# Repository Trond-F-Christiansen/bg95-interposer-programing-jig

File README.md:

# nRF9151-MK-BG95 interposer programmer

A pogo-pin jig that gives the PCA10196 BG95 interposer (an nRF9151 on a BG95 footprint) power
and a UART AT interface, so the Serial Modem firmware and modem firmware can be programmed and
tested without soldering. SWD is connected with a separate cable.

## Contents

| Folder | What it holds |
|---|---|
| `pcb/` | KiCad project of the pogo-pin plate (`bg95-pogo-plate`), BOM, gerbers in `production/`, and local footprints, 3D models in `lib/` |
| `3d-model/` | 3D-printed frame parts (`.3mf/.step`) and `Assembly.png` |
| `fw/bg95_programmer_at_interface/` | nRF54LM20 DK app: AT shell that forwards typed lines to the interposer |
| `fw/flash_and_verify.py` | Programs modem firmware and app, then checks AT and the modem version |
| `fw/*.hex`, `fw/*.zip` | Serial Modem v2.0.0 release image and modem firmware `mfw_nrf91x1_2.0.4` |

## How it works

Six spring probes land on the BG95 footprint pads of the interposer. The same PCB is used as
upper and lower plate to keep the probes aligned. Receptacles are only soldered into the upper one.

| Header J2 | Signal | BG95 pad | DK pin |
|---|---|---|---|
| 1 | VDD | 32/33 and 52/53 (VBAT_BB, VBAT_RF) | 3.0 V to 5.5 V supply |
| 2 | GND | GND pads | GND |
| 3 | DBG_TX | 23 (interposer TX, P0.15) | P1.04 (UART21 RX) |
| 4 | DBG_RX | 22 (interposer RX, P0.14) | P1.03 (UART21 TX) |

* Supply voltage: **3.0 V to 5.5 V**.
* UART: 115200 8N1, no flow control. The interposer uses 1.8 V I/O, so set the DK's `VDD_IO` to
  **1.8 V**.
* Pads 22 and 23 are adjacent, so their probes are staggered.

## Programming

Hardware: an nRF54LM20 DK running `fw/bg95_programmer_at_interface`, wired to the jig as above.
The DK's on-board debugger is routed out through its debug-out header, with a cable to the
interposer's SWD connector, and programs the nRF9151.

### SWD cable

A custom cable connects the DK's 10-pin debug-out connector to the interposer's 20-pin SWD
connector:

* The 10-pin end plugs into the DK debug-out connector. The 20-pin end plugs into the interposer.
* Pin 1 is pin 1 on both ends, and pins 1 to 10 are wired one-to-one.
* Pins 11 to 20 of the 20-pin connector are left unconnected.

### Flashing

```bash
uv run fw/flash_and_verify.py \
    --port /dev/cu.usbmodem<DK serial>3 \
    --app fw/serial_modem_v2.0.0_interposer_nrf9151_mk_bg95_nrf91m1.hex \
    --modem-fw fw/mfw_nrf91x1_2.0.4.zip
```

The script recovers the device (erases flash and UICR), programs the modem firmware and then the
app, resets, and checks that `AT` returns `OK` and `AT+CGMR` reports the expected modem firmware.
`--sn` is only needed if more than one J-Link is connected. `--port` is the DK's VCOM port.

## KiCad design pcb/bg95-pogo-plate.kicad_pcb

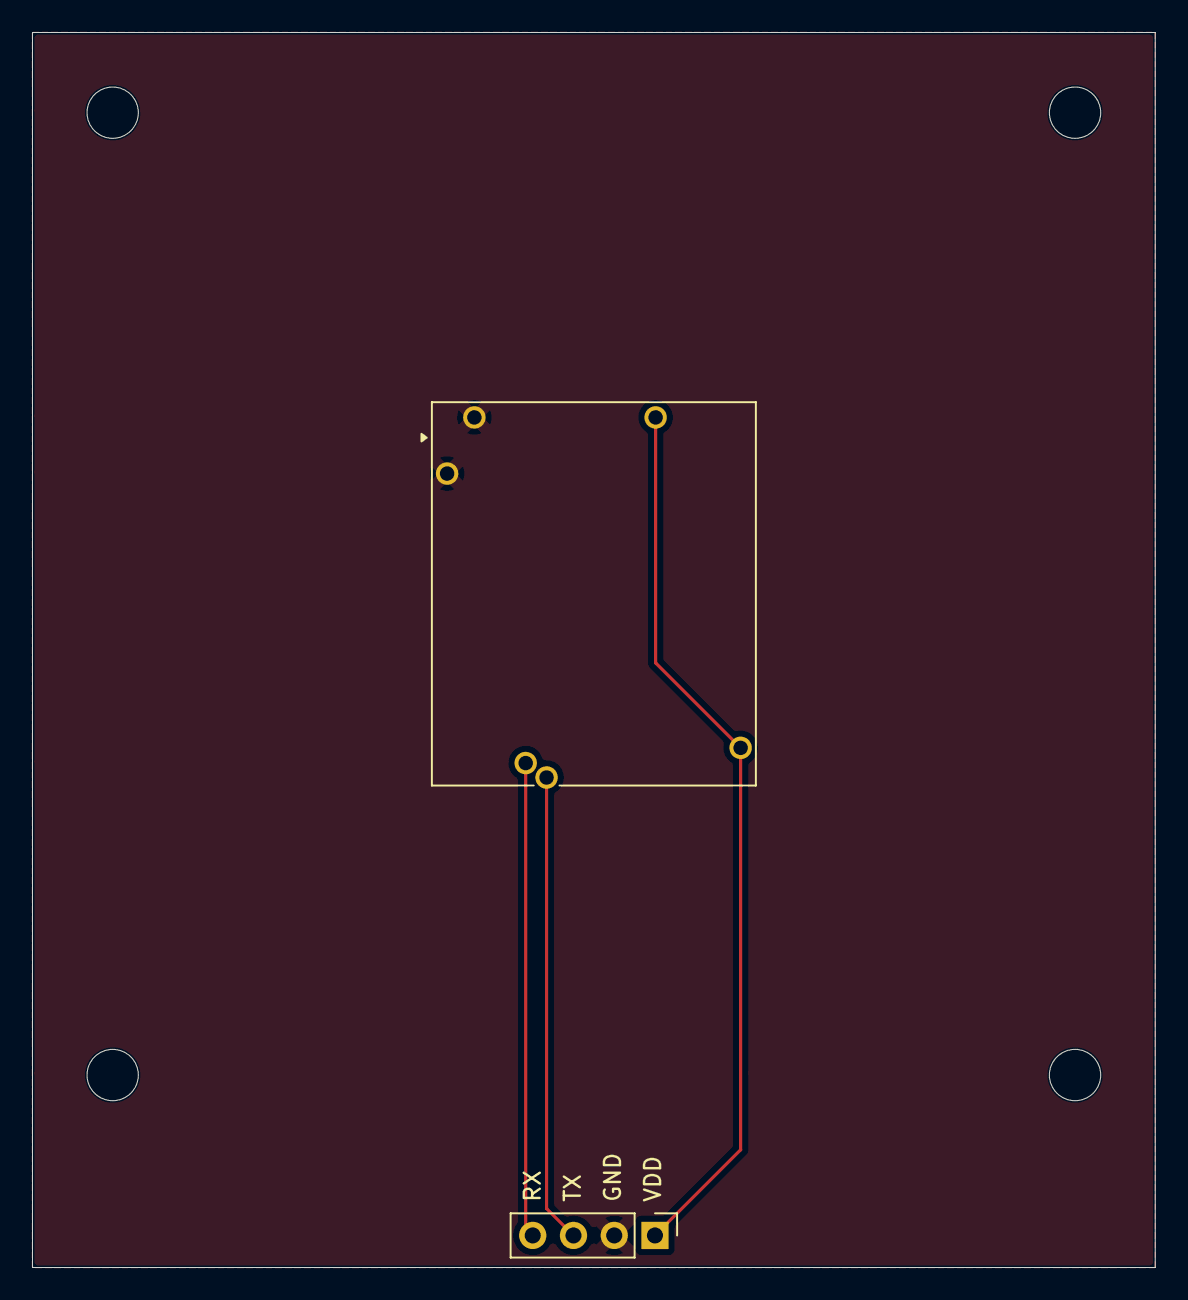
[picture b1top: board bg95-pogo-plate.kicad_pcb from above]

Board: 2 copper layers, 70.0 x 77.0 mm, 11 parts (0 on the bottom side), 4 nets.

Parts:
H1, H2, H3, H4: MountingHole; MountingHole_3.2mm_M3
J1: Conn_01x02_Pin; P50_R50SC_Lower_StaggerPair_1.3x0.9_PTH_D0.90_Pad1.40
J2: Conn_01x04_Pin; PinHeader_1x04_P2.54mm_Vertical
J3, J4, J5, J6: Conn_01x01_Pin; P50_R50SC_Lower_PTH_D0.90_Pad1.40
U1: BG95-M1; Quectel_BG95_UserDwgs

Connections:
/DBG_RX(bg95-22): J1.1, J2.4
/DBG_TX(bg95-23: J1.2, J2.3
/GND: J2.2, J5.1, J6.1
/VDD: J2.1, J3.1, J4.1

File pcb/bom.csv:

Reference,Qty,Description,Manufacturer,Part number,Notes
J1;J3;J4;J5;J6,6,"Spring probe (pogo pin), 1.27 mm pitch family",Multicomp,P50-B-120-G,"J1 is the staggered DBG_RX/DBG_TX pair; J3,J4 = VDD; J5,J6 = GND."
J1;J3;J4;J5;J6,6,"Receptacle (socket) for P50 probes, solder cup",Multicomp,R50-SC,"Soldered into the lower plate."
J2,1,"Pin header, 1x04, 2.54 mm, vertical",Generic,,"1 VDD, 2 GND, 3 DBG_TX (BG95 pad 23), 4 DBG_RX (BG95 pad 22)"
,,"",,,""
,,"",,,""
